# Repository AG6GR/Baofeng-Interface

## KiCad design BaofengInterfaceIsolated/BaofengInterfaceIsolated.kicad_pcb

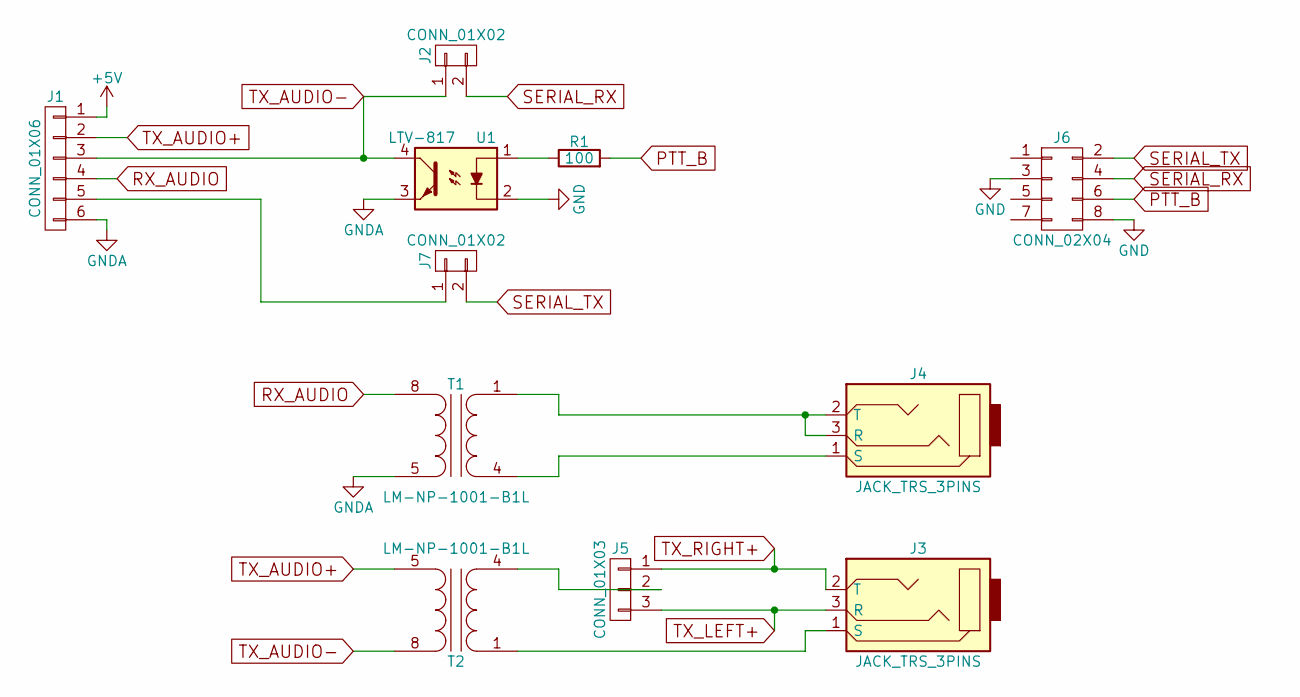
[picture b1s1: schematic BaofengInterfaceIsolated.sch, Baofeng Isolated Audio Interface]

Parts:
J1: CONN_01X06; Pin_Header_Straight_1x06_Pitch2.54mm
J2, J7: CONN_01X02; Pin_Header_Straight_1x02_Pitch2.54mm
J3, J4: JACK_TRS_3PINS; SJ1-352XN; MFRPN SJ1-3523N
J5: CONN_01X03; Pin_Header_Straight_1x03_Pitch2.54mm
J6: CONN_02X04; Pin_Header_Straight_2x04_Pitch2.54mm
R1: 100; R_Axial_DIN0207_L6.3mm_D2.5mm_P2.54mm_Vertical
T1, T2: LM-NP-1001-B1L; LM-LP-1001L; MFRPN LM-NP-1001-B1L
U1: LTV-817; DIP-4_W7.62mm; MFRPN LTV-817

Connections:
+5V: J1.1
GND: J6.3, J6.8, U1.2
GNDA: J1.6, T1.5 (SA), U1.3
unnamed: J1.5, J7.1
unnamed: J3.1 (S), T2.1 (AA)
unnamed: J4.1 (S), T1.4 (AB)
unnamed: J4.2 (T), J4.3 (R), T1.1 (AA)
unnamed: J5.2, T2.4 (AB)
unnamed: R1.1, U1.1
PTT_B: J6.6, R1.2
RX_AUDIO: J1.4, T1.8 (SB)
SERIAL_RX: J2.2, J6.4
SERIAL_TX: J6.2, J7.2
TX_AUDIO+: J1.2, T2.5 (SA)
TX_AUDIO-: J1.3, J2.1, T2.8 (SB), U1.4
TX_LEFT+: J3.3 (R), J5.3
TX_RIGHT+: J3.2 (T), J5.1

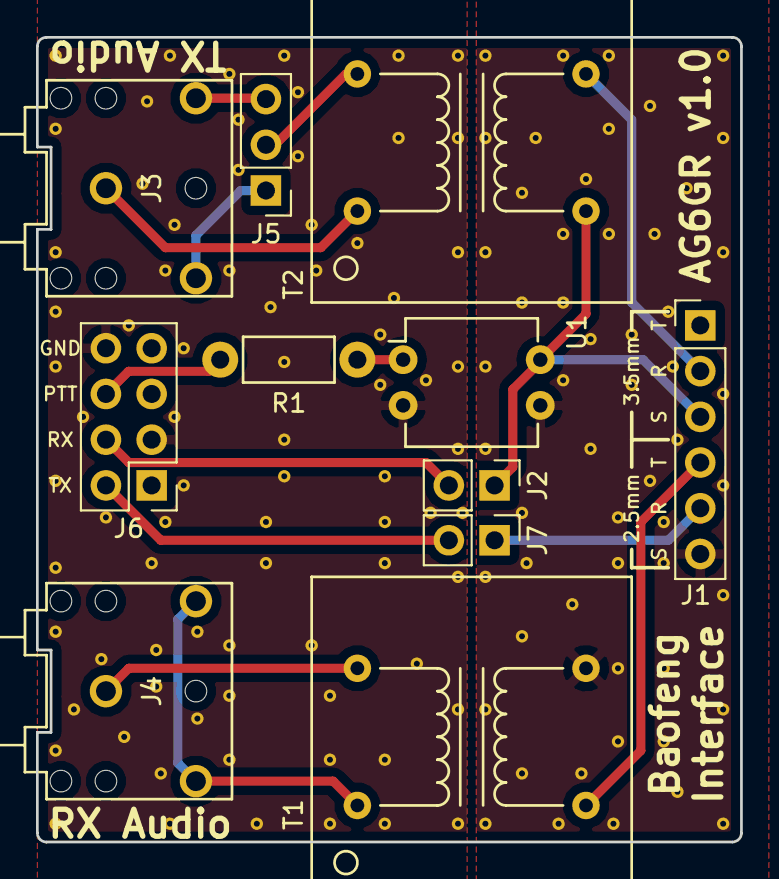
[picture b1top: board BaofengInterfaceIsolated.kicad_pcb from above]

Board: 2 copper layers, 39.1 x 44.7 mm, 11 parts (0 on the bottom side), 16 nets.

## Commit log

2017-05-29 PCB layou finish
2017-05-29 Add 3D model for audio jack
2017-05-30 Add isolated design
2017-05-30 Cleanup board edge, silkscreen
2017-06-10 Finish Via Stitching
2017-06-10 Submit rev 1 to Oshpark
2017-07-17 Add board documentation and gerbers
